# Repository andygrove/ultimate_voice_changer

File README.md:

# Ultimate Voice Changer Arduino Library

## What is this?

This is the official Arduino library for the Ultimate Voice Changer Arduino Shield, which is an open source hardware project that uses an MCP3208 ADC and an MCP4921 DAC with SPI communications to provide high quality voice sampling and real-time audio manipulation.

## Shield PCB

Eagle schematics and board layout for an Arduino Uno shield are included in this repository. Boards can also be purchased directly from OSH Park:

* [Ultimate Voice Changer PCB @ OSH Park](https://oshpark.com/shared_projects/ojPzRnSB)

## Component List

* [MCP3204](https://www.mouser.com/ProductDetail/579-MCP3204-CI-P)
* [MCP4921](https://www.mouser.com/ProductDetail/579-MCP4921-E-P)
* [Audio Jack](https://www.mouser.com/ProductDetail/502-35RAPC4BHN2)
* 1K resistor
* 1.5K resistor
* 330 ohm resistor
* 0.1 uF capacitor
* [10 uF electrolytic capacitor (2mm spacing)](https://www.mouser.com/ProductDetail/667-ECA-1HM100)
* [LED T1-3/4 (5mm) RED](https://www.mouser.com/ProductDetail/696-SLX-LX5093ID)
* [36-pin header](https://www.mouser.com/ProductDetail/538-22-28-4363)
* [10K Trimpot](https://www.sparkfun.com/products/9806)

## Example sketches

See the [examples](examples) directory for Dalek / ring modulator examples that mix voice input with a sine wave for robotic voice effects.

## Alternatives

I am no longer actively maintaining this project or providing support and I would suggest looking at the [Adafruit Wave Shield](https://learn.adafruit.com/wave-shield-voice-changer/overview) instead. They even have an example Dalek sketch.

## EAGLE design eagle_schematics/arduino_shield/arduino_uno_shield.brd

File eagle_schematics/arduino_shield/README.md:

# Arduino Shield

This directory contains Eagle schematics and board layout for an Arduino shield version of the voice changer that is compatible with the Arduino Uno R3.

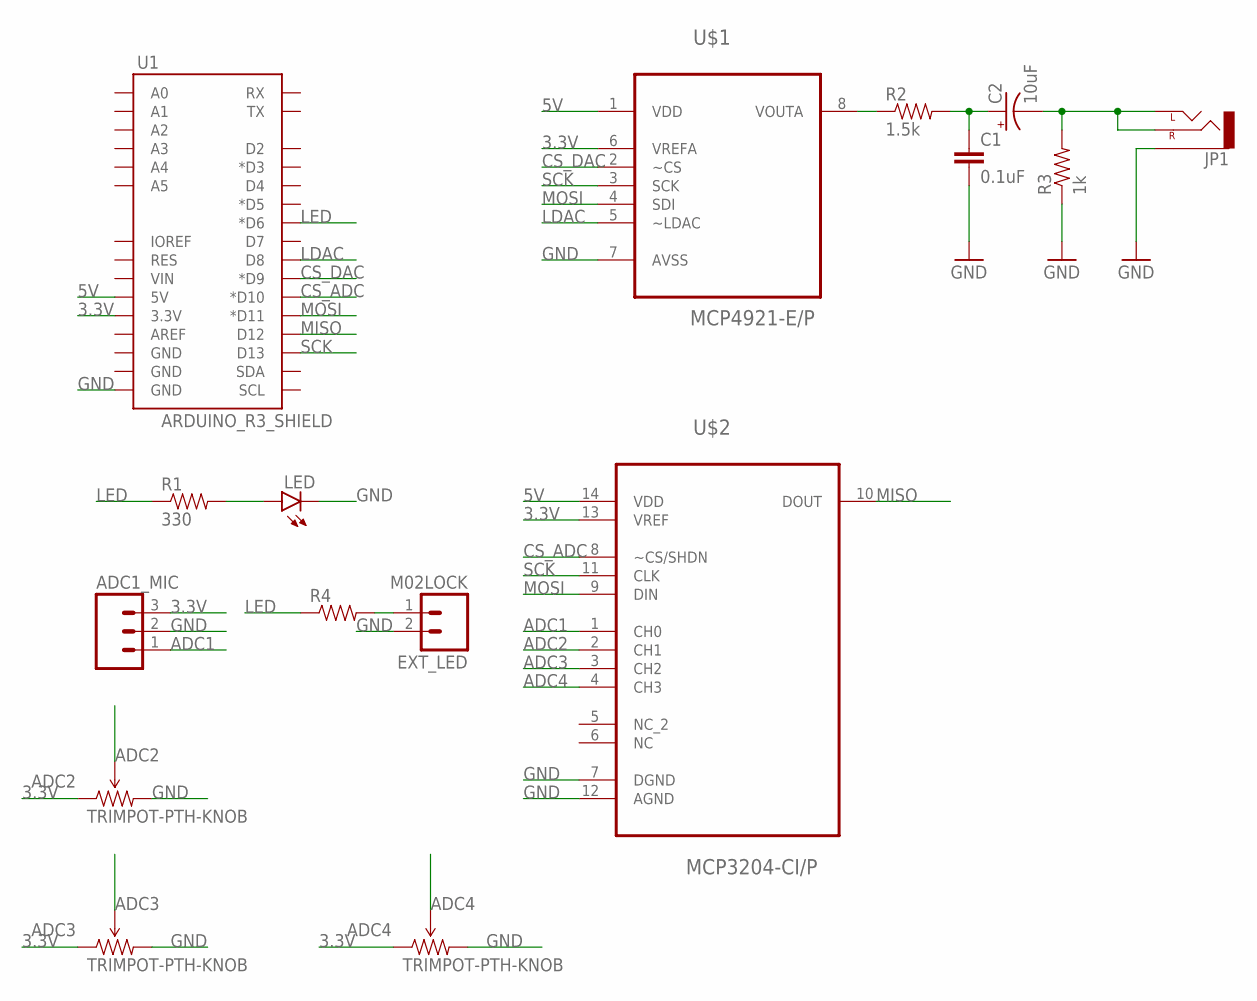
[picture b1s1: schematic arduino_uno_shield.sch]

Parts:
ADC1_MIC: M03LOCK; 1X03_LOCK
ADC2, ADC3, ADC4: TRIMPOT-PTH-KNOB; 3386U
C1: 0.1uF; CAP-PTH-5MM
C2: 10uF; CPOL-RADIAL-10UF-25V
EXT_LED: M02LOCK; 1X02_LOCK
JP1: AUDIO-JACKPTH; AUDIO-JACK
LED: LED5MM
R1: 330; AXIAL-0.4
R2: 1.5k; AXIAL-0.4
R3: 1k; AXIAL-0.4
R4: RESISTORPTH-1/4W; AXIAL-0.4
U1: ARDUINO_R3_SHIELD; UNO_R3_SHIELD
U$1: MCP4921-E/P; DIP254P762X432-8
U$2: MCP3204-CI/P; DIP254P762X432-14

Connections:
3.3V: ADC1_MIC.3, ADC2.1 (CCW), ADC3.1 (CCW), ADC4.1 (CCW), U1.3.3V, U$1.6 (VREFA), U$2.13 (VREF)
5V: U1.5V, U$1.1 (VDD), U$2.14 (VDD)
ADC1: ADC1_MIC.1, U$2.1 (CH0)
ADC2: ADC2.2 (WIPER), U$2.2 (CH1)
ADC3: ADC3.2 (WIPER), U$2.3 (CH2)
ADC4: ADC4.2 (WIPER), U$2.4 (CH3)
CS_ADC: U1.D10 (*D10), U$2.8 (~CS/SHDN)
CS_DAC: U1.D9 (*D9), U$1.2 (~CS)
GND: ADC1_MIC.2, ADC2.3 (CW), ADC3.3 (CW), ADC4.3 (CW), C1.2, EXT_LED.2, JP1.SLEEVE, LED.K (C), R3.P$1 (1), U1.GND@0 (GND), U$1.7 (AVSS), U$2.7 (DGND), U$2.12 (AGND)
LDAC: U1.D8, U$1.5 (~LDAC)
LED: R1.P$1 (1), R4.P$1 (1), U1.D6 (*D6)
MISO: U1.D12, U$2.10 (DOUT)
MOSI: U1.D11 (*D11), U$1.4 (SDI), U$2.9 (DIN)
unnamed: LED.A, R1.P$2 (2)
unnamed: R2.P$1 (1), U$1.8 (VOUTA)
unnamed: C1.1, C2.1 (+), R2.P$2 (2)
unnamed: C2.2 (-), JP1.RING (RIGHT), JP1.TIP (LEFT), R3.P$2 (2)
unnamed: EXT_LED.1, R4.P$2 (2)
SCK: U1.D13, U$1.3 (SCK), U$2.11 (CLK)

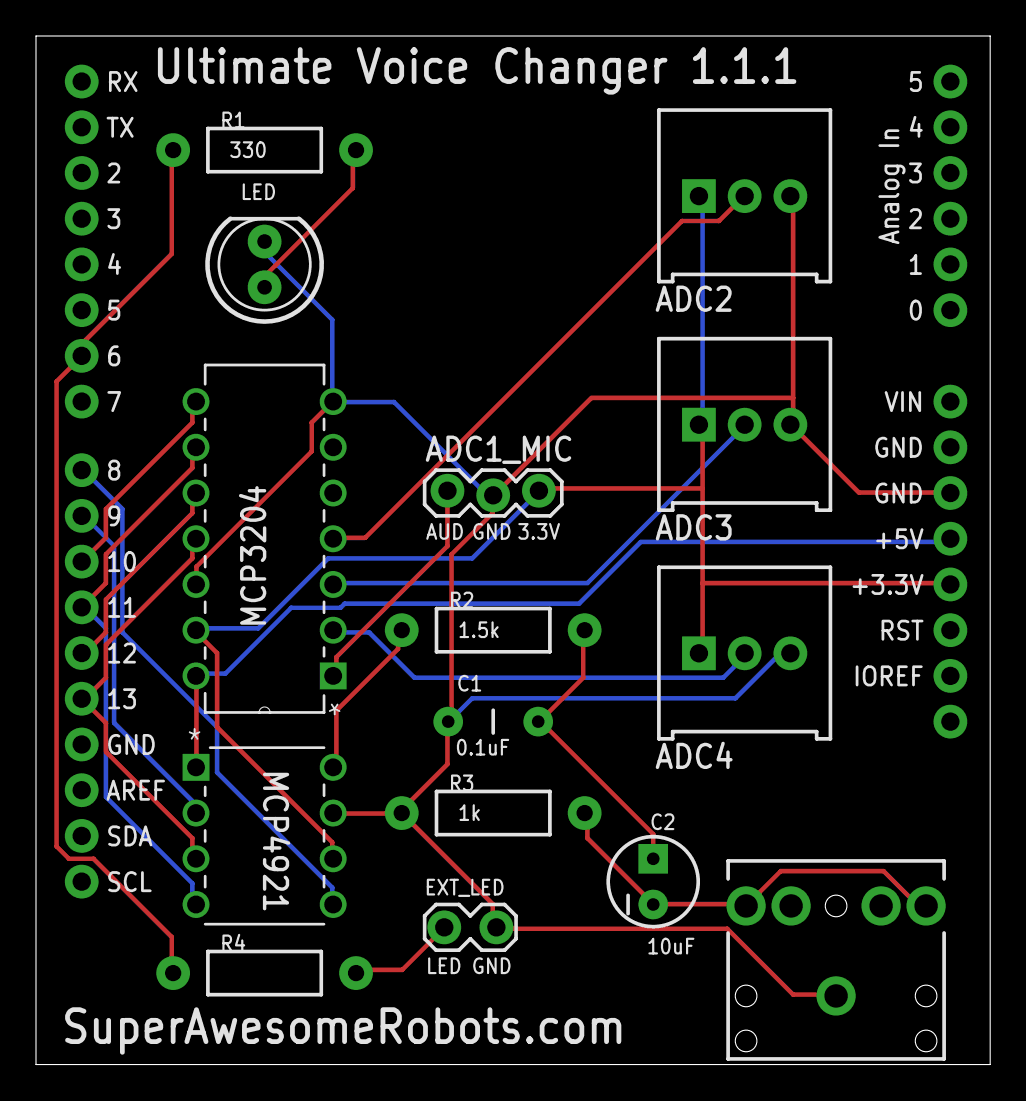
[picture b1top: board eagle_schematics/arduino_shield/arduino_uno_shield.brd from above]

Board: 2 copper layers, 53.0 x 57.1 mm, 16 parts (0 on the bottom side), 19 nets.

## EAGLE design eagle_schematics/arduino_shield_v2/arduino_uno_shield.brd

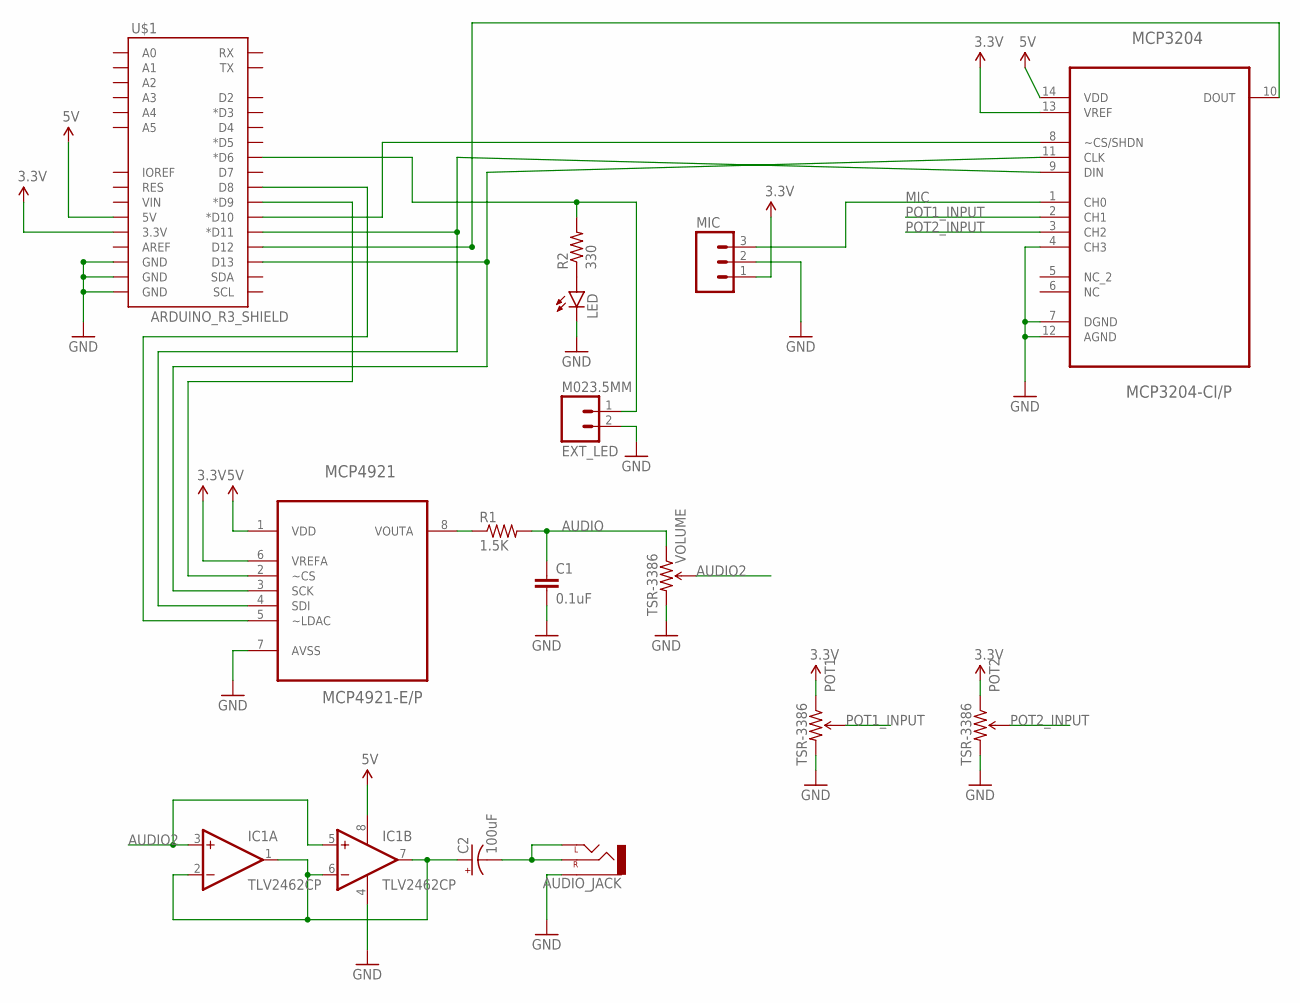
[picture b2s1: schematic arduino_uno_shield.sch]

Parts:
AUDIO_JACK: AUDIO-JACKPTH; AUDIO-JACK
C1: 0.1uF; CAP-PTH-SMALL
C2: 100uF; CPOL-RADIAL-100UF-25V
EXT_LED: M023.5MM; SCREWTERMINAL-3.5MM-2
IC1: TLV2462CP; DIL08
LED: LED5MM
MCP3204: MCP3204-CI/P; DIP254P762X432-14
MCP4921: MCP4921-E/P; DIP254P762X432-8
MIC: M03PTH; 1X03
POT1, POT2: TSR-3386; 3386U
R1: 1.5K; AXIAL-0.4
R2: 330; AXIAL-0.4
U$1: ARDUINO_R3_SHIELD; UNO_R3_SHIELD
VOLUME: TSR-3386; 3386U

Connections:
3.3V: MCP3204.13 (VREF), MCP4921.6 (VREFA), MIC.1, POT1.1 (CCW), POT2.1 (CCW), U$1.3.3V
5V: IC1.8 (V+), MCP3204.14 (VDD), MCP4921.1 (VDD), U$1.5V
AUDIO: C1.1, R1.P$2 (2), VOLUME.1 (CCW)
AUDIO2: IC1.3 (+IN), IC1.5 (+IN), VOLUME.2 (WIPER)
CS_ADC: MCP3204.8 (~CS/SHDN), U$1.D10 (*D10)
CS_DAC: MCP4921.2 (~CS), U$1.D9 (*D9)
GND: AUDIO_JACK.SLEEVE, C1.2, EXT_LED.2, IC1.4 (V-), LED.K (C), MCP3204.4 (CH3), MCP3204.7 (DGND), MCP3204.12 (AGND), MCP4921.7 (AVSS), MIC.2, POT1.3 (CW), POT2.3 (CW), U$1.GND@0 (GND), U$1.GND@1 (GND), U$1.GND@2 (GND), VOLUME.3 (CW)
MIC: MCP3204.1 (CH0), MIC.3
unnamed: MCP4921.8 (VOUTA), R1.P$1 (1)
unnamed: C2.1 (+), IC1.1 (OUT), IC1.2 (-IN), IC1.6 (-IN), IC1.7 (OUT)
unnamed: AUDIO_JACK.RING (RIGHT), AUDIO_JACK.TIP (LEFT), C2.2 (-)
unnamed: LED.A, R2.P$1 (1)
unnamed: MCP4921.5 (~LDAC), U$1.D8
unnamed: EXT_LED.1, R2.P$2 (2), U$1.D6 (*D6)
POT1_INPUT: MCP3204.2 (CH1), POT1.2 (WIPER)
POT2_INPUT: MCP3204.3 (CH2), POT2.2 (WIPER)
SPI_CLK: MCP3204.11 (CLK), MCP4921.3 (SCK), U$1.D13
SPI_MISO: MCP3204.10 (DOUT), U$1.D12
SPI_MOSI: MCP3204.9 (DIN), MCP4921.4 (SDI), U$1.D11 (*D11)

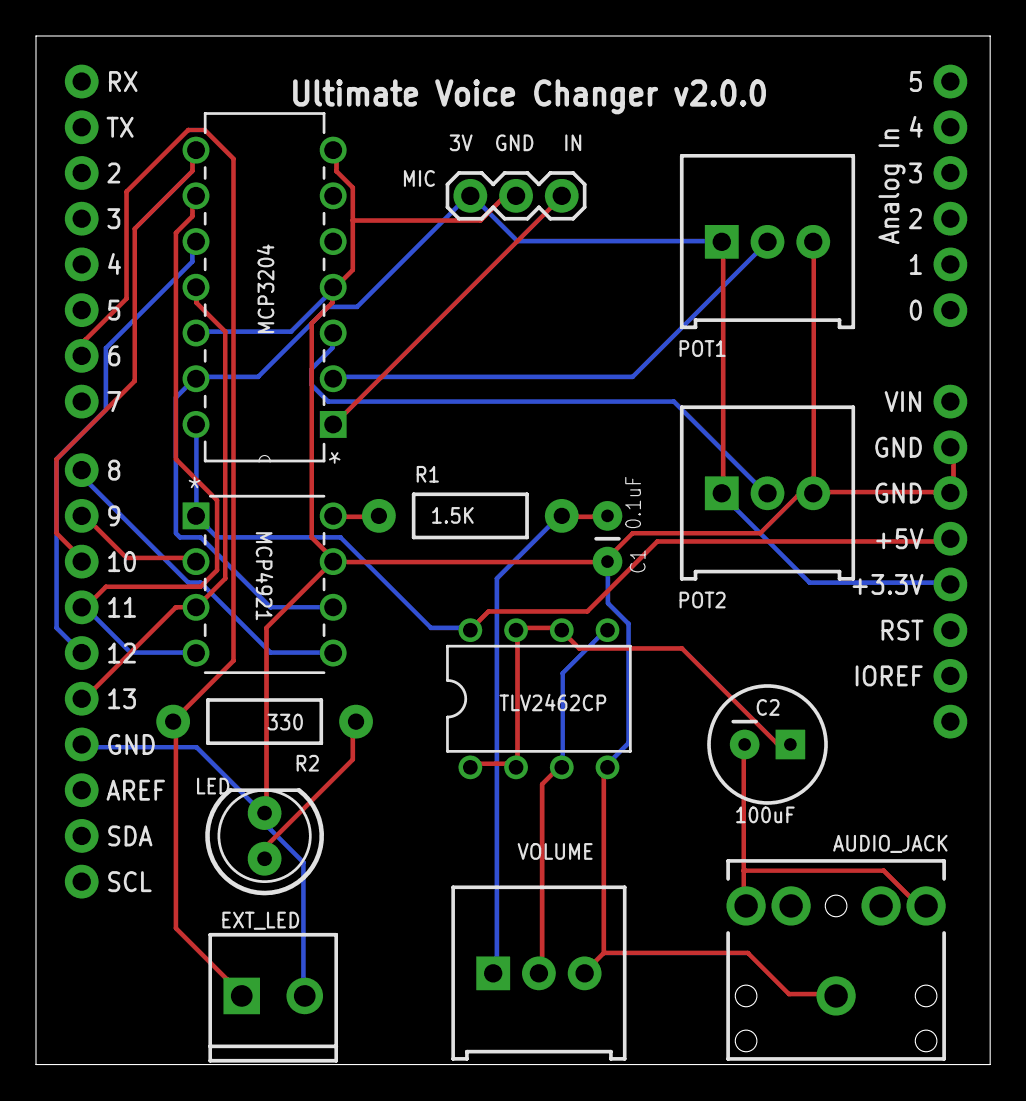
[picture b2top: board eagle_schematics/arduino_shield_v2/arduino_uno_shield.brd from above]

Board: 2 copper layers, 53.0 x 57.1 mm, 15 parts (0 on the bottom side), 19 nets.

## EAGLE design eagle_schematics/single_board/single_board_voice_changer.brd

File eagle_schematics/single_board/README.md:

# Single Board Version

This is an experimental single-board version of the voice changer that incorporates an ATMEGA238P so that no separate Arduino board is required.

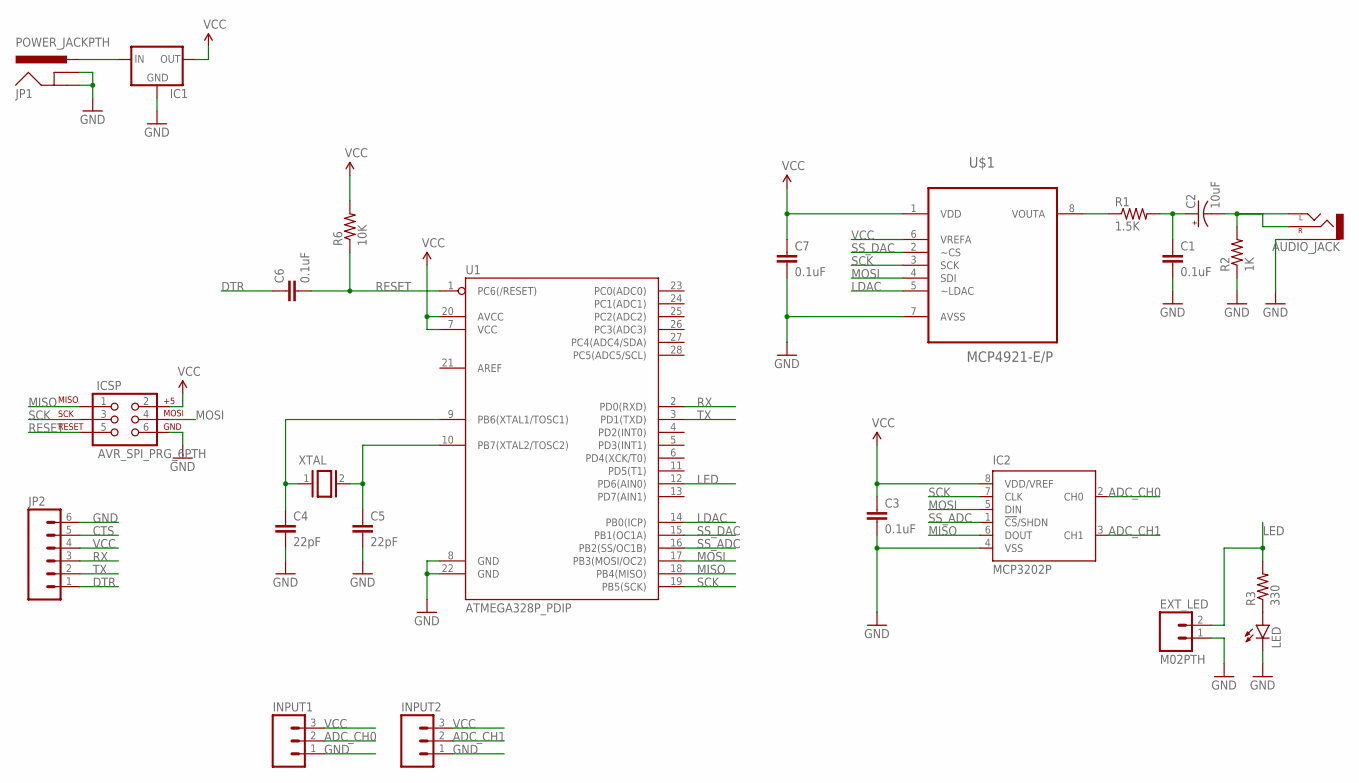
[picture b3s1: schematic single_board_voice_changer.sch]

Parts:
AUDIO_JACK: AUDIO-JACKPTH; AUDIO-JACK
C1, C3, C6, C7: 0.1uF; CAP-PTH-SMALL
C2: 10uF; CPOL-RADIAL-10UF-25V
C4, C5: 22pF; CAP-PTH-SMALL
EXT_LED: M02PTH; 1X02
IC1: V_REG_78XXSIDE; 78XXL
IC2: MCP3202P; DIL8
ICSP: AVR_SPI_PRG_6PTH; 2X3
INPUT1, INPUT2: M03PTH; 1X03
JP1: POWER_JACKPTH; POWER_JACK_PTH
JP2: M06SILK_FEMALE_PTH; 1X06
LED: LED5MM
R1: 1.5K; AXIAL-0.4
R2: 1K; AXIAL-0.4
R3: 330; AXIAL-0.4
R6: 10K; AXIAL-0.4
U1: ATMEGA328P_PDIP; DIL28-3
U$1: MCP4921-E/P; DIP254P762X432-8
XTAL: XTAL/S; QS

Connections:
ADC_CH0: IC2.2 (CH0), INPUT1.2
ADC_CH1: IC2.3 (CH1), INPUT2.2
CTS: JP2.5
DTR: C6.1, JP2.1
GND: AUDIO_JACK.SLEEVE, C1.2, C3.2, C4.2, C5.2, C7.2, EXT_LED.1, IC1.GND, IC2.4 (VSS), ICSP.6, INPUT1.1, INPUT2.1, JP1.GND, JP1.GNDBREAK, JP2.6, LED.K (C), R2.P$1 (1), U1.8 (GND), U1.22 (GND), U$1.7 (AVSS)
LDAC: U1.14 (PB0(ICP)), U$1.5 (~LDAC)
LED: EXT_LED.2, R3.P$2 (2), U1.12 (PD6(AIN0))
MISO: IC2.6 (DOUT), ICSP.1, U1.18 (PB4(MISO))
MOSI: IC2.5 (DIN), ICSP.4, U1.17 (PB3(MOSI/OC2)), U$1.4 (SDI)
unnamed: R1.P$1 (1), U$1.8 (VOUTA)
unnamed: C1.1, C2.1 (+), R1.P$2 (2)
unnamed: LED.A, R3.P$1 (1)
unnamed: IC1.IN, JP1.PWR
unnamed: C4.1, U1.9 (PB6(XTAL1/TOSC1)), XTAL.1
unnamed: C5.1, U1.10 (PB7(XTAL2/TOSC2)), XTAL.2
unnamed: AUDIO_JACK.RING (RIGHT), AUDIO_JACK.TIP (LEFT), C2.2 (-), R2.P$2 (2)
RESET: C6.2, ICSP.5, R6.P$1 (1), U1.1 (PC6(/RESET))
RX: JP2.3, U1.2 (PD0(RXD))
SCK: IC2.7 (CLK), ICSP.3, U1.19 (PB5(SCK)), U$1.3 (SCK)
SS_ADC: IC2.1 (!CS!/SHDN), U1.16 (PB2(SS/OC1B))
SS_DAC: U1.15 (PB1(OC1A)), U$1.2 (~CS)
TX: JP2.2, U1.3 (PD1(TXD))
VCC: C3.1, C7.1, IC1.OUT, IC2.8 (VDD/VREF), ICSP.2, INPUT1.3, INPUT2.3, JP2.4, R6.P$2 (2), U1.7 (VCC), U1.20 (AVCC), U$1.1 (VDD), U$1.6 (VREFA)

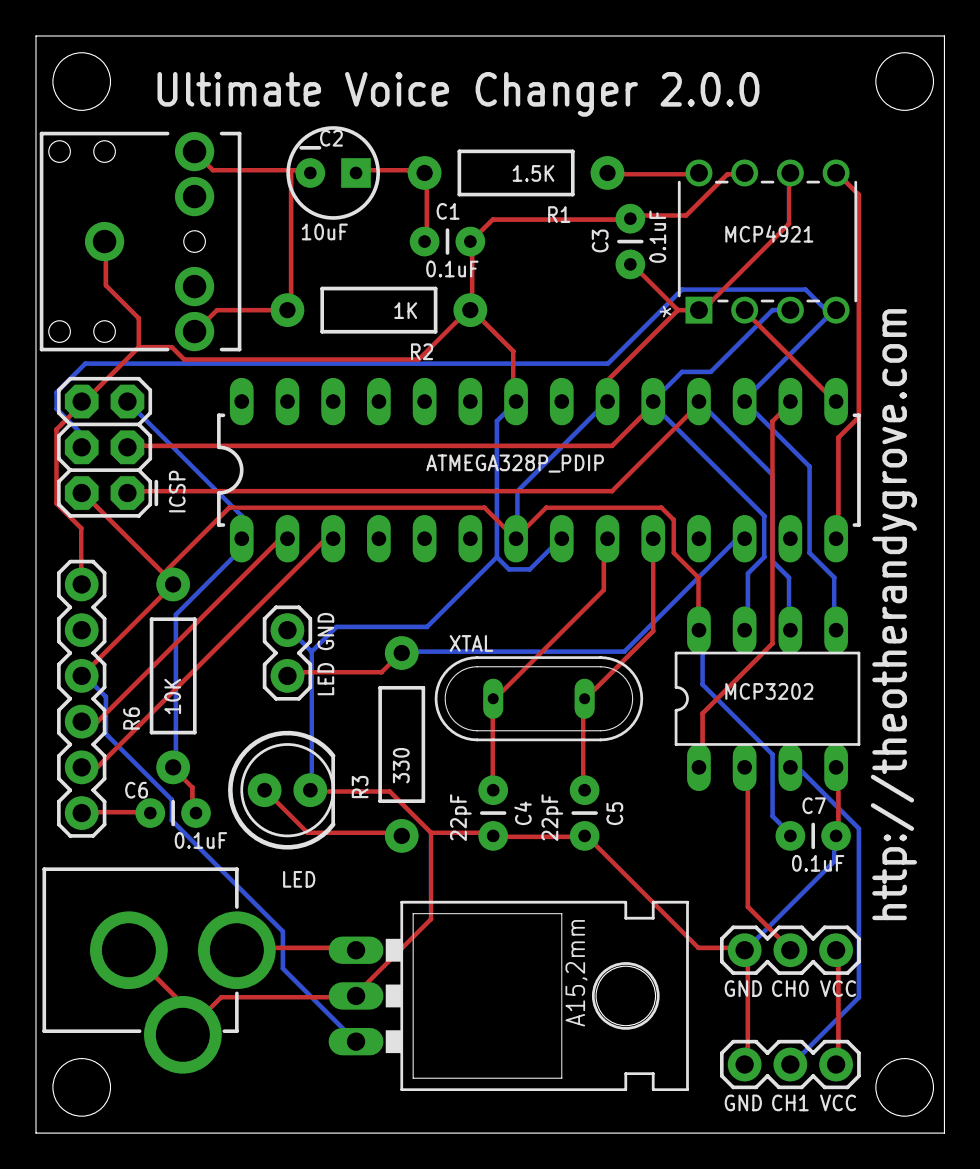
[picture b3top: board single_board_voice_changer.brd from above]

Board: 2 copper layers, 50.5 x 61.0 mm, 24 parts (0 on the bottom side), 22 nets.

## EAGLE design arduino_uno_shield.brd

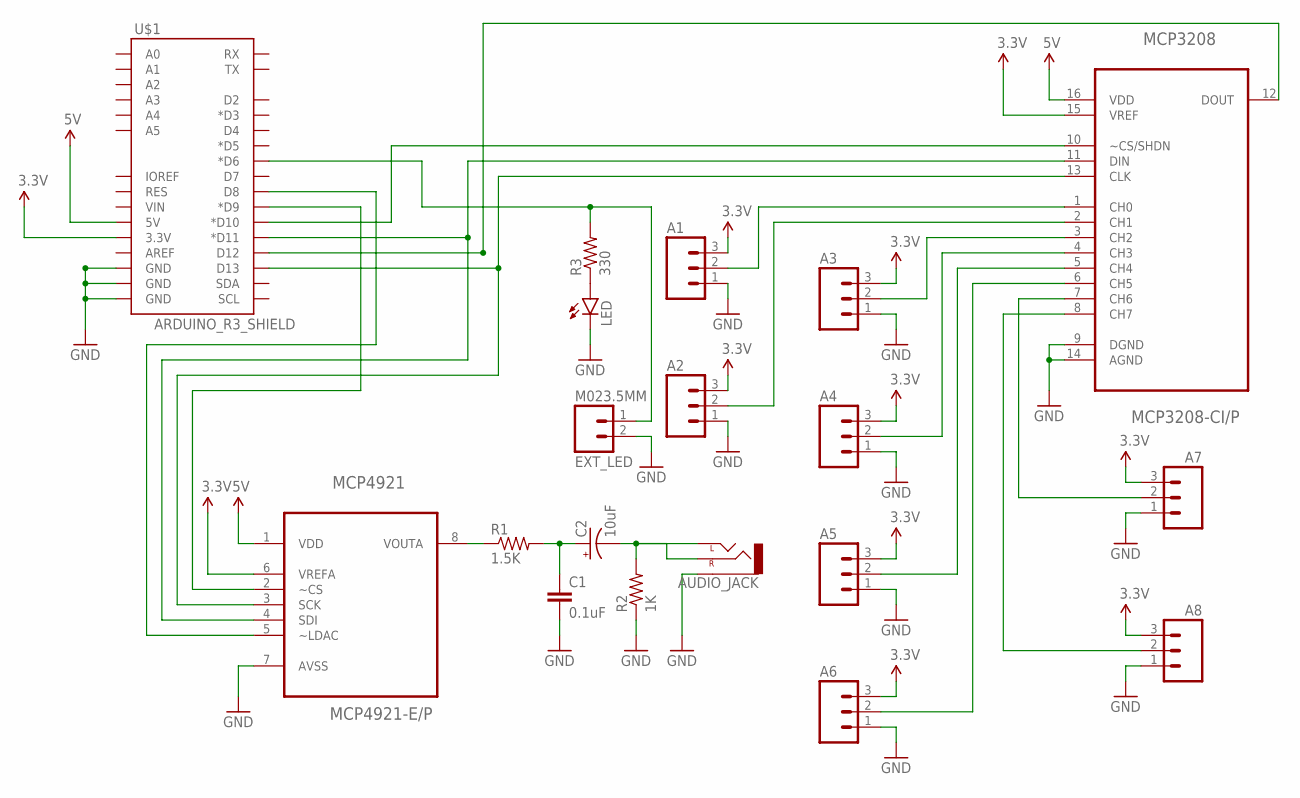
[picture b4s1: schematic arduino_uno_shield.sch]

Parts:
A1, A2, A3, A4, A5, A6, A7, A8: M03PTH; 1X03
AUDIO_JACK: AUDIO-JACKPTH; AUDIO-JACK
C1: 0.1uF; CAP-PTH-SMALL
C2: 10uF; CPOL-RADIAL-10UF-25V
EXT_LED: M023.5MM; SCREWTERMINAL-3.5MM-2
LED: LED5MM
MCP3208: MCP3208-CI/P; DIP254P762X432-16
MCP4921: MCP4921-E/P; DIP254P762X432-8
R1: 1.5K; AXIAL-0.4
R2: 1K; AXIAL-0.4
R3: 330; AXIAL-0.4
U$1: ARDUINO_R3_SHIELD; UNO_R3_SHIELD

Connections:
3.3V: A1.3, A2.3, A3.3, A4.3, A5.3, A6.3, A7.3, A8.3, MCP3208.15 (VREF), MCP4921.6 (VREFA), U$1.3.3V
5V: MCP3208.16 (VDD), MCP4921.1 (VDD), U$1.5V
AUD: A1.2, MCP3208.1 (CH0)
CS_ADC: MCP3208.10 (~CS/SHDN), U$1.D10 (*D10)
CS_DAC: MCP4921.2 (~CS), U$1.D9 (*D9)
GND: A1.1, A2.1, A3.1, A4.1, A5.1, A6.1, A7.1, A8.1, AUDIO_JACK.SLEEVE, C1.2, EXT_LED.2, LED.K (C), MCP3208.9 (DGND), MCP3208.14 (AGND), MCP4921.7 (AVSS), R2.P$1 (1), U$1.GND@0 (GND), U$1.GND@1 (GND), U$1.GND@2 (GND)
unnamed: A5.2, MCP3208.5 (CH4)
unnamed: A2.2, MCP3208.2 (CH1)
unnamed: MCP4921.8 (VOUTA), R1.P$1 (1)
unnamed: C1.1, C2.1 (+), R1.P$2 (2)
unnamed: AUDIO_JACK.RING (RIGHT), AUDIO_JACK.TIP (LEFT), C2.2 (-), R2.P$2 (2)
unnamed: LED.A, R3.P$1 (1)
unnamed: MCP4921.5 (~LDAC), U$1.D8
unnamed: EXT_LED.1, R3.P$2 (2), U$1.D6 (*D6)
unnamed: A3.2, MCP3208.3 (CH2)
unnamed: A4.2, MCP3208.4 (CH3)
unnamed: A6.2, MCP3208.6 (CH5)
unnamed: A7.2, MCP3208.7 (CH6)
unnamed: A8.2, MCP3208.8 (CH7)
SPI_CLK: MCP3208.13 (CLK), MCP4921.3 (SCK), U$1.D13
SPI_MISO: MCP3208.12 (DOUT), U$1.D12
SPI_MOSI: MCP3208.11 (DIN), MCP4921.4 (SDI), U$1.D11 (*D11)

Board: 2 copper layers, 20 parts (0 on the bottom side), 22 nets, no tracks yet.

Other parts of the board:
FRAME3: FRAME-LETTER; CREATIVE_COMMONS

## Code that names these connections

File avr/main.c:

/**
 * Ultimate Voice Changer for Arduino/AVR.
 *
 * Requires an external board/shield hosting an MCP3208 ADC and an MCP4921 DAC.
 *
 * Created by Andy Grove.
 * http://theotherandygrove.com
 */

#include <avr/io.h>
#include <avr/power.h>
#include <avr/interrupt.h>
#include <util/delay.h>

#include "wave.h"

// PORTB pin assignments
const int LDAC = 0;     // PB0 / Arduino pin 8
const int CS_DAC = 1;   // PB1 / Arduino pin 9
const int CS_ADC = 2;   // PB2 / Arduino pin 10
const int DATAOUT = 3;  // PB3 / Arduino pin 11
const int DATAIN = 4;   // PB4 / Arduino pin 12
const int SPICLOCK = 5; // PB5 / Arduino pin 13

// SPI command for DAC
const int cmd = 0x7000;

const long n = 10000;

int myindex = 0;
int fword = 0;
uint8_t data = 0;
int counter = 0;
long last_time = 0;

void setup(void) {

  // set clock to full speed (8 MHz)
  //clock_prescale_set(clock_div_1);

  // disable interrupts
  //cli();

  // we're not using the onboard ADC so may as well power it down
  //power_adc_disable();

  // LDAC, CS_DAC, CS_ADC, DATAOUT to OUTPUT
  DDRB |= (1 << LDAC);
  DDRB |= (1 << CS_ADC);
  DDRB |= (1 << CS_DAC);
  DDRB |= (1 << DATAOUT);
  DDRB |= (1 << SPICLOCK);

  // set DATAIN to INPUT
  DDRB &= ~_BV(DATAIN);

  // LED 
  DDRD |= _BV(7);

  // disable both the ADC and DAC by writing them HIGH
  PORTB |= (1 << CS_ADC);
  PORTB |= (1 << CS_DAC);

  // set the clock low
  PORTB &= ~(1 << SPICLOCK);

}

inline int pot_to_incr(int pot) {
  return 1 + (pot/64);
}

/** Set CLK HIGH then LOW */
inline void cycle_clock(void) {
  PORTB |= (1 << SPICLOCK);
  PORTB &= ~(1 << SPICLOCK);
}

/** Read from ADC */
int read_adc(int channel){

  int adcvalue = 0;

  // command bits - start, mode, chn (3), dont care (3)
  int commandbits = 0xC0; //b11000000; 

  // allow channel selection
  commandbits|=((channel-1)<<3);

  // select ADC
  PORTB &= ~(1 << CS_ADC);

  // setup bits to be written
  for (int i=7; i>=3; i--){
    if (commandbits&1<<i) {
      PORTB |= (1 << DATAOUT);
    } else {
      PORTB &= ~(1 << DATAOUT);
    }
    cycle_clock();
  }

  //cycle clock twice to ignore two null bits
  cycle_clock();
  cycle_clock();

  //read bits from adc
  for (int i=11; i>=0; i--){
    adcvalue += ((PINB & _BV(DATAIN)) >> 4) << i;
    cycle_clock();
  }

  PORTB |= (1 << CS_ADC);

  return adcvalue;
}

/** Write to DAC */
void write_dac(int data) {

  // combine command and data
  fword = cmd | data;
  
  // chip select
  PORTB &= ~_BV(CS_DAC);
  
  // start writing data
  PORTB |= _BV(LDAC);

  for (int i1=0; i1<16; i1++) {
    if (fword & 0x8000) {
      PORTB |= _BV(DATAOUT);
    } else {
      PORTB &= ~_BV(DATAOUT);
    }

    cycle_clock();

    fword = fword << 1; 
  }

  // end of conversion
  PORTB |= _BV(CS_DAC);
  
  // writing data to output buffer
  PORTB &= ~_BV(LDAC);
}

int incr = 1;

int dc_bias = 0;

int audio_in;

int sample_counter = 0;

/** debug routine to make sure AVR is working. */
void blink(void) {
  setup();
  while (1) {
    PORTD ^= (1 << 7);
    _delay_ms(200);
  }
}

/** play the sine wave through the DAC. */
void play_sine_wave(void) {
  setup();
  int multiplier = 16;
  int increment = 1; // 1=30 Hz, 2=60Hz, 3=90Hz ... 7=210 Hz
  int i = 0;
  int j = 0;
  while (1) {

    if (++j==400) {
      j = 0;
      increment = pot_to_incr(read_adc(2));
    }

    uint8_t s = pgm_read_byte(&sineWave[i]);

    write_dac((multiplier*127)+((s-127)*multiplier));

    // increment the index in the wave table
    i += increment;
    if (i>=NUM_SINE_WAVE_POINTS) {
      i -= NUM_SINE_WAVE_POINTS;
    }
  }
}

void ring_modulator(void) {

  setup();

  while(1) {

    ++sample_counter;

    if (sample_counter == 400) {
      incr = pot_to_incr(read_adc(2));
      sample_counter = 0;
    } else {
      // sample audio input
      audio_in = read_adc(1);
    }

    // get next point in sine wave table
    myindex += incr;
    if (myindex >= NUM_SINE_WAVE_POINTS)  {
      myindex -= NUM_SINE_WAVE_POINTS;
    }
    //data = sineWave[myindex];
    data = pgm_read_byte(&sineWave[myindex]);

    // mix audio with sine wave
    audio_in = 2047 + ((audio_in-2047) * ((data-127) / 127.0));

    // clip the signal
    if (audio_in<0) audio_in = 0;
    else if (audio_in>4095) audio_in = 4095;
    
    // write output
    write_dac(audio_in);
  }

}

int main(void) {
  // choose a routine to call	  
  //blink();
  //play_sine_wave();
  ring_modulator();
  return 0;
}

    

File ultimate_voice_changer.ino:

/**
 * Ultimate Voice Changer for Arduino
 * Created by Andy Grove.
 *
 * Requires an external board/shield hosting an MCP3208 ADC 
 * and an MCP4921 DAC as well as a few passive components and
 * an audio jack.
 *
 * For more information, please visit the project page:
 *
 * http://theotherandygrove.com/projects/ultimate-voice-changer-arduino-shield/
 */

// comment this out if you don't want the LED working
#define ENABLE_LED 

// comment this out if you don't have a pot attached to the second input
#define ENABLE_POT

// the code now supports some different effects modes, mostly to help with debugging
#define MODE_NO_EFFECT 1 // this mode passes the mic input directly to the audio out without modification
#define MODE_RING_MOD  2 // this is the default ring modulator mode where the mic input is mixed with a sine wave then written to audio out
#define MODE_SINE_WAVE 3 // this mode writes the sine wave directly to audio out

const int mode = MODE_RING_MOD;

// number of points in sine wave data
#define NUM_SINE_WAVE_POINTS 1024

// PORTD pin assignments
const int PORTD_LED = 6;

// uncomment this line to use MCP3202 instead of MCP3204/8
//#define MCP3202

// PORTB pin assignments
const int LDAC = 0;     // Arduino pin 8
const int CS_DAC = 1;   // Arduino pin 9
const int CS_ADC = 2;   // Arduino pin 10
const int DATAOUT = 3;  // Arduino pin 11
const int DATAIN = 4;   // Arduino pin 12
const int SPICLOCK = 5; // Arduino pin 13

// SPI command for DAC
const int cmd = 0x7000;

// threshold for tuning sensitivity of LED response to sound levels
const int threshold = 256;

int index = 0;
int fword;
int data;
int counter = 0;
long last_time = 0;

// speed to iterate over sine wave .. changing this affects the frequency
int incr = 2;

// this variable is used for the LED PWM effect
int sound_level = 0;
int led_counter = 0;
int sample_counter = 0;
int audio_in = 0;
int audio_out = 0;
int dc_offset = 2063;

byte sineWave[NUM_SINE_WAVE_POINTS];  

void setup() {
  
  // prepare sine wave
  fill_sinewave();

  delay(1000);

  cli();
  
  // set digital pin 6 to output for the LEDs
  DDRD |= _BV(PORTD_LED);

  // LDAC, CS_DAC, CS_ADC, DATAOUT to OUTPUT
  DDRB |= _BV(LDAC);
  DDRB |= _BV(CS_ADC);
  DDRB |= _BV(CS_DAC);
  DDRB |= _BV(DATAOUT);
  DDRB |= _BV(SPICLOCK);

  // set DATAIN to INPUT
  DDRB &= ~_BV(DATAIN);

  // disable both the ADC and DAC by writing them HIGH
  PORTB |= _BV(CS_ADC);
  PORTB |= _BV(CS_DAC);

  // set the clock low
  PORTB &= ~_BV(SPICLOCK);
  
  // turn the LED on briefly to show startup
  PORTD |= _BV(PORTD_LED);
  delay(500);
  PORTD &= ~_BV(PORTD_LED);
}

/** Set CLK HIGH then LOW */
inline void cycle_clock() {
  PORTB |= _BV(SPICLOCK);
  PORTB &= ~_BV(SPICLOCK);
}

/** Read from ADC */
int read_adc_mcp3202(int channel){

  int adcvalue = 0;

  // command bits - start, sgl/diff, odd/sign, channel 0, channel 1
  byte commandbits = B11010000; 

  // allow channel selection
  commandbits|=((channel-1)<<5);

  // select ADC
  PORTB &= ~_BV(CS_ADC);

  // setup bits to be written
  for (int i=7; i>=4; i--){
    if (commandbits&1<<i) {
      PORTB |= _BV(DATAOUT);
    } else {
      PORTB &= ~_BV(DATAOUT);
    }
    cycle_clock();
  }

  //cycle clock to ignore null bit
  cycle_clock();

  //read bits from adc
  for (int i=11; i>=0; i--){
    adcvalue += ((PINB & _BV(DATAIN)) >> 4) << i;
    cycle_clock();
  }

  PORTB |= _BV(CS_ADC);

  return adcvalue;
}

/** Read from ADC */
int read_adc_mcp3208(int channel){

  int adcvalue = 0;

  // command bits - start, mode, chn (3), dont care (3)
  byte commandbits = B11000000; 

  // allow channel selection
  commandbits|=((channel-1)<<3);

  // select ADC
  PORTB &= ~_BV(CS_ADC);

  // setup bits to be written
  for (int i=7; i>=3; i--){
    if (commandbits&1<<i) {
      PORTB |= _BV(DATAOUT);
    } else {
      PORTB &= ~_BV(DATAOUT);
    }
    cycle_clock();
  }

  //cycle clock twice to ignore two null bits
  cycle_clock();
  cycle_clock();

  //read bits from adc
  for (int i=11; i>=0; i--){
    adcvalue += ((PINB & _BV(DATAIN)) >> 4) << i;
    cycle_clock();
  }

  PORTB |= _BV(CS_ADC);

  return adcvalue;
}

int read_adc(int channel){
#ifdef MCP3202
  return read_adc_mcp3202(channel);
#else
  return read_adc_mcp3208(channel);
#endif
}

/** Write to DAC */
void write_dac(int data) {

  // combine command and data
  fword = cmd | data;
  
  // chip select
  PORTB &= ~_BV(CS_DAC);
  
  // start writing data
  PORTB |= _BV(LDAC);

  for (int i1=0; i1<16; i1++) {
    if (fword & 0x8000) {
      PORTB |= _BV(DATAOUT);
    } else {
      PORTB &= ~_BV(DATAOUT);
    }

    cycle_clock();

    fword = fword << 1; 
  }

  // end of conversion
  PORTB |= _BV(CS_DAC);
  
  // writing data to output buffer
  PORTB &= ~_BV(LDAC);
}

void loop() {

  ++sample_counter;

  if (sample_counter == 400) {
    sample_counter = 0;
    
#ifdef ENABLE_POT
    int pot = read_adc(2);
    incr = 1 + (pot/128);
#endif

  } else {
    // sample audio input
    audio_in = read_adc(1);
  }

  // get next point in sine wave table
  index += incr;
  if (index >= NUM_SINE_WAVE_POINTS)  {
    index -= NUM_SINE_WAVE_POINTS;
  }
  data = sineWave[index];

  // mix audio with sine wave
  if (mode == MODE_SINE_WAVE) {
    audio_in = 4095;
    audio_out = 2047 + ((audio_in-dc_offset) * ((data-127) / 127.0));
  } else if (mode == MODE_RING_MOD) {
    audio_out = 2047 + ((audio_in-dc_offset) * ((data-127) / 127.0));
  } else {
    audio_out = audio_in;
  }
  
#ifdef ENABLE_LED

  if (audio_in > 2048+threshold || audio_in < 2048-threshold) {
    sound_level = 255;
  } else {
    if (sound_level > 0) {
      sound_level -= 1;
    }
  }
  
  // crude way to simulate PWM effect, this could be improved by using interrupts
  if (++led_counter > 255) {
    led_counter = 0;
  }
  if (led_counter < sound_level) {
    PORTD |= _BV(PORTD_LED);
  } else {
    PORTD &= ~_BV(PORTD_LED);
  }

#endif

  // clip the signal
  if (audio_out<0) audio_out = 0;
  else if (audio_out>4095) audio_out = 4095;

  // attempt to reduce noise
  if (audio_out > 2030 && audio_out < 2100) {
    audio_out = 2047;
  }
  
  // write output
  write_dac(audio_out);
}

void fill_sinewave(){
  float pi = 3.141592;
  float dx = dx = 2 * pi / NUM_SINE_WAVE_POINTS;   // fill the  byte bufferarry
  float fd = 0;
  float fcnt = 0;
  int iw;
  for (iw = 0; iw < NUM_SINE_WAVE_POINTS; iw++){      // with 50 periods sinewawe
    fd= 127*sin(fcnt);                // fundamental tone
    fcnt=fcnt+dx;                     // in the range of 0 to 2xpi  and 1/512 increments
    int bb=127+fd;                        // add dc offset to sinewawe 
    sineWave[iw]=bb;                  // write value into array
    // uncomment this to see the sine wave numbers in the serial monitor
    
    Serial.print("Sine: ");
    Serial.println(bb);
    
  }
}    
    

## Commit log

2014-10-11 initial checkin of sample code
2014-10-11 write_dac function
2014-10-11 now reads from adc and passes value to dac
2014-10-11 blink LED to show sampling rate
2014-10-11 optimizing
2014-10-11 ring mod effect works
2014-10-11 code cleanup
2014-10-12 converting to pure AVR code
2014-10-12 remove unused macros
2014-10-12 remove unused const
2014-10-12 save
2014-10-18 set SPICLOCK to OUTPUT
2014-10-20 started on schematics
2014-10-20 wiring up schematic
2014-10-20 first attempt at board layout
2014-10-20 removed board
2014-10-20 remove project
2014-10-20 re-created board
2014-10-21 clean up board layout
2014-10-21 add more pot headers
2014-10-21 created board from scratch
2014-10-21 fixed polarity issue on LED screw terminal
2014-10-21 save latest
2014-10-29 first cut of AVR version
2014-10-29 init vars
2014-10-29 set clock speed
2014-10-30 avr version working
2014-11-02 enable LED
2014-11-03 changed layout to reduce interference
2014-11-03 add branding
2014-11-14 remove avr code
2014-11-14 refining board layout to remove via:
2014-11-14 saving work, this version ordered
2014-12-29 roughing out pre-amp schematic
2014-12-30 udpated schematic for pre-amp
2015-04-02 started work on single board version
2015-05-03 working on single board version
2015-05-03 board with no ground plane, 0
2015-05-03 price down to 8.77
2015-05-08 add support for MCP3202 ADC
2015-05-12 change ADC to MCP3202
2015-05-12 redo board
2015-05-13 another rev of the board design
2015-05-13 consistent fonts
2015-05-29 fix error with schematic
2015-11-27 code cleanup and make it easier to test sine wave output without ring mod effect
2015-12-28 add noise canceling code
2016-01-01 restructure as library
2016-01-01 code compiles
2016-01-01 convert sinewave to class
2016-01-01 add sinewave class, move debug example
2016-01-01 restruture repo
2016-01-02 Add Dalek sketch with fixed frequencies
2016-01-03 start work on new version of shield
2016-01-03 add amplifier
2016-01-03 working on new board layout with trimpots
2016-01-03 change to MCP3204 with 2 trimpot inputs
2016-01-04 refine board layout
2016-03-01 new board rev
2016-03-03 clean up board
2016-03-15 small refinement to board layout
2016-03-15 remove experimental designs
2016-03-15 change resistors from AXIAL-0.3 to AXIAL-0.4
2016-06-09 update for version 1.1 of board (use channel 0 for pot instead of channel 2)

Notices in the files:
parts and their libraries:
SparkFun-Connectors: Licensing: Creative Commons ShareAlike 4.0 International - https://creativecommons.org/licenses/by-sa/4.0
SparkFun-Aesthetics: Released under the Creative Commons Attribution Share-Alike 4.0 License
SparkFun-Aesthetics: https://creativecommons.org/licenses/by-sa/4.0
